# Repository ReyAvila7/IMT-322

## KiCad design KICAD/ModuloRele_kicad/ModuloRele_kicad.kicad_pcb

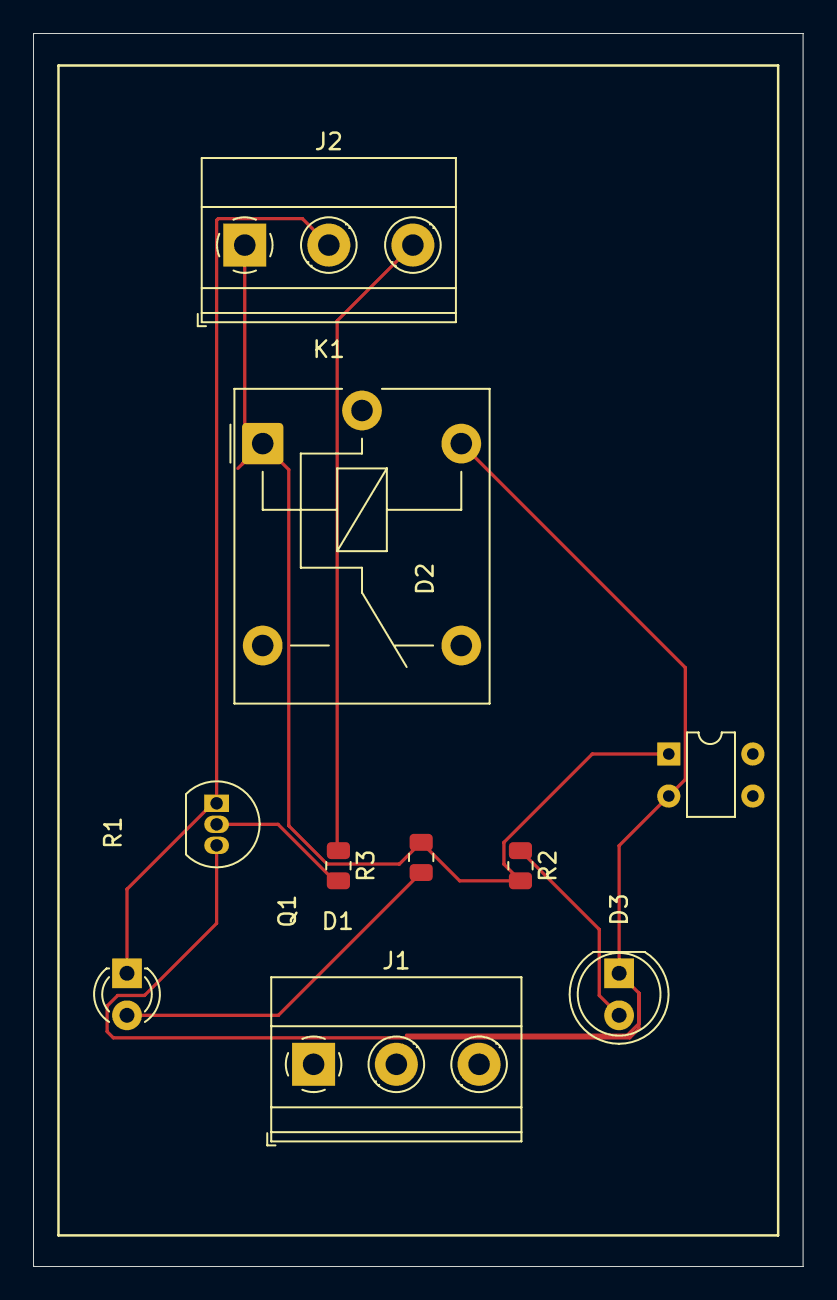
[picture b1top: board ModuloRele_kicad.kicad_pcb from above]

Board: 2 copper layers, 46.5 x 74.5 mm, 10 parts (0 on the bottom side), 7 nets.

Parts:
D1: D; Diode_Bridge_DIP-4_W5.08mm_P2.54mm
D2: LED; LED_D3.0mm
D3: LED; LED_D5.0mm_IRGrey
J1: Conn_01x03_Pin; TerminalBlock_Phoenix_MKDS-1,5-3_1x03_P5.00mm_Horizontal
J2: Conn_01x03_Pin; TerminalBlock_Phoenix_MKDS-1,5-3-5.08_1x03_P5.08mm_Horizont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
K1: Relay_SPDT; Relay_SPDT_Finder_36.11
Q1: S8050; TO-92_Inline
R1, R2, R3: R; R_0805_2012Metric

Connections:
unnamed: D1.2 (A), D3.1 (K), K1.A2, Q1.3 (C)
unnamed: D1.1 (K), J2.1, K1.A1, R1.2, R2.2
unnamed: D2.2 (A), R1.1
unnamed: D2.1 (K), J2.2, Q1.1 (E)
unnamed: D3.2 (A), R2.1
unnamed: J2.3, R3.1
unnamed: Q1.2 (B), R3.2

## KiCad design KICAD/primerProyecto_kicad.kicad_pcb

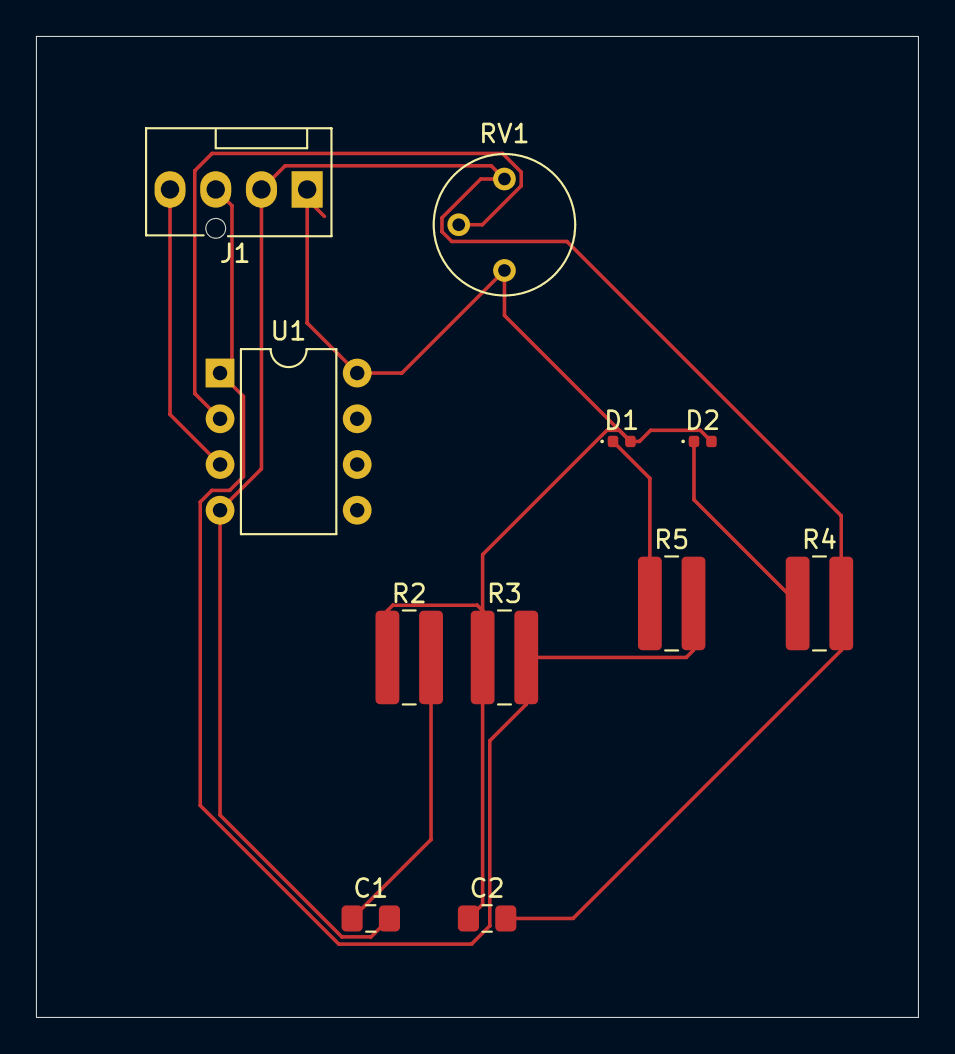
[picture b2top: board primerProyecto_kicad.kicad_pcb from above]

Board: 2 copper layers, 49.0 x 54.5 mm, 11 parts (0 on the bottom side), 8 nets.

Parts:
C1, C2: 1 uF; C_0805_2012Metric_Pad1.18x1.45mm_HandSolder
D1, D2: LED; LED_0402_1005Metric
J1: Conn_01x04; FanPinHeader_1x04_P2.54mm_Vertical
R2, R3: 10 K; R_1020_2550Metric_Pad1.33x5.20mm_HandSolder
R4, R5: 1; R_1020_2550Metric_Pad1.33x5.20mm_HandSolder
RV1: Pot 10 k; Potentiometer_Bourns_3339P_Vertical
U1: LM393; DIP-8_W7.62mm

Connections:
GND: C1.2, C2.2, J1.2, R4.2, RV1.3, U1.4 (V-)
unnamed: C1.1, R2.2
unnamed: D1.1 (K), R5.1
unnamed: D2.1 (K), R4.1
unnamed: J1.3, R3.2, R5.2, U1.1
unnamed: J1.4, U1.3 (+)
unnamed: RV1.2, U1.2 (-)
VCC: C2.1, D1.2 (A), D2.2 (A), J1.1, R2.1, R3.1, RV1.1, U1.8 (V+)

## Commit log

2024-02-17 reynaldo
2024-02-17 NANITO
2024-02-24 punto 1, ejercicio
2024-02-24 Modificación 24/02
2024-03-02 Practica 2, Interrupciones
2024-03-02 practica 2.2
2024-03-09 Practica3.1
2024-03-19 Examen Parcial Practico
2024-04-06 Primera PCB
2024-04-21 SENSOR DE PROXIMIDAD
2024-04-21 Codigo y diagrama
2024-04-21 Maquinas de estado finito
2024-04-22 Placa PCB_Modulo_Relé
2024-04-25 Ascensor
2024-04-27 Examen practico2
2024-05-21 prueba blink
2024-05-28 Codigo de examen practico
